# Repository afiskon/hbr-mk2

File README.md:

# HBR/MK2

All HF bands QRP CW/SSB transceiver "HomeBrew Radio, Mark 2".

* Covers 80, 40, 30, 20, 17, 15, 12 and 10 meters
* Classical single IF superheterodyne design
* Effective IF derived AGC
* Voice compression
* Supports RIT and XIT
* 10-30 WPM Elekey-B type keyer + straight key mode
* Keyer supports record and playback, programmable with paddles
* Five favorite frequencies per band (press NEXT/PREV in FAST mode)
* Class AB amplifier provides 5-10W in both CW and SSB
* Has a S-meter and a SWR meter
* Open-source firmware, schematic and 3D-printable enclosure

Links:

* Article (in Russian): https://eax.me/2024/2024-05-12-hbr-mk2-transceiver.html
* Post on Hackaday: https://hackaday.com/2024/05/13/github-hosts-ham-radio/
* Post on DXZone: https://www.dxzone.com/hbr-mk2-hf-qrp-cw-ssb-transceiver/
* Video blog on YouTube: https://www.youtube.com/playlist?list=PL6CWlCy5akj5v1Z4mPysYlqgNtCBYy-wM
* Video blog on Archive.org: https://archive.org/details/hbr-mk2-videos

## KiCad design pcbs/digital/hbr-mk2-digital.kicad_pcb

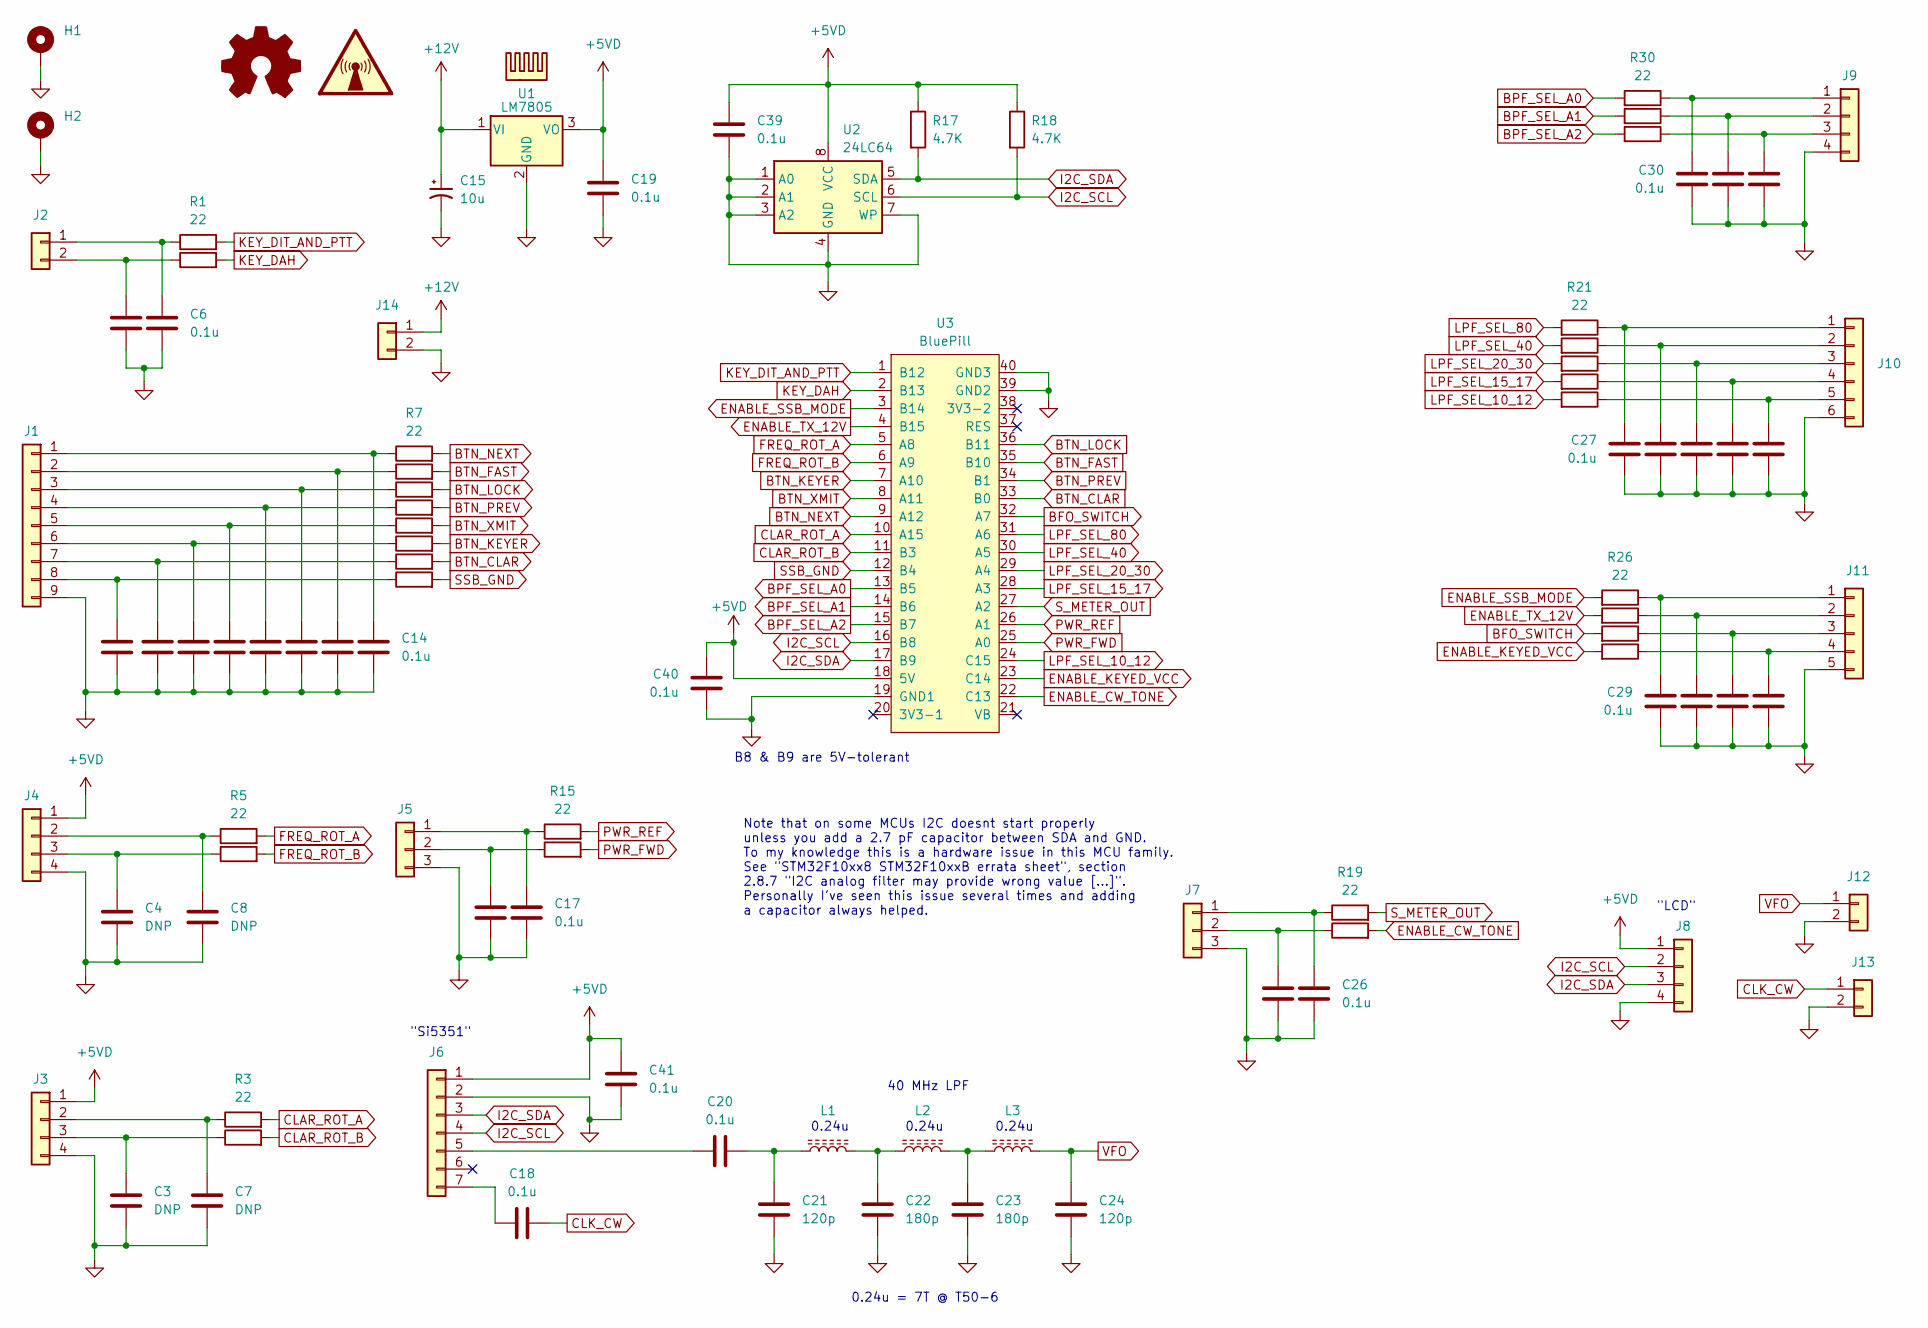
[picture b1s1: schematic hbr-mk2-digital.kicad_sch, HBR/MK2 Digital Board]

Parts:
C1, C2, C5, C6, C9, C10, C11, C12, C13, C14, C16, C17, C18, C19, C20, C25, C26, C27, C28, C29, C30, C31, C32, C33, C34, C35, C36, C37, C38, C39, C40, C41: 0.1u; C_0805_2012Metric_Pad1.18x1.45mm_HandSolder
C3, C4, C7, C8: DNP; C_0805_2012Metric_Pad1.18x1.45mm_HandSolder
C15: 10u; CP_Radial_D5.0mm_P2.50mm
C21, C24: 120p; C_0805_2012Metric_Pad1.18x1.45mm_HandSolder
C22, C23: 180p; C_0805_2012Metric_Pad1.18x1.45mm_HandSolder
H1, H2: MountingHole_Pad; MountingHole_3.5mm_Pad_Via
HS1: Heatsink
J1: Conn_01x09; PinHeader_1x09_P2.54mm_Vertical
J2, J12, J13, J14: Conn_01x02; PinHeader_1x02_P2.54mm_Vertical
J3, J4, J8, J9: Conn_01x04; PinHeader_1x04_P2.54mm_Vertical
J5, J7: Conn_01x03; PinHeader_1x03_P2.54mm_Vertical
J6: Conn_01x07; PinHeader_1x07_P2.54mm_Vertical
J10: Conn_01x06; PinHeader_1x06_P2.54mm_Vertical
J11: Conn_01x05; PinHeader_1x05_P2.54mm_Vertical
L1, L2, L3: T50-6; L_Toroid_Vertical_L13.0mm_W6.5mm_P5.60mm
R1, R2, R3, R4, R5, R6, R7, R8, R9, R10, R11, R12, R13, R14, R15, R16, R19, R20, R21, R22, R23, R24, R25, R26, R27, R28, R29, R30, R31, R32: 22; R_0805_2012Metric_Pad1.20x1.40mm_HandSolder
R17, R18: 4.7K; R_0805_2012Metric_Pad1.20x1.40mm_HandSolder
SYM1: Logo_Open_Hardware_Small; OSHW-Logo2_9.8x8mm_SilkScreen
SYM2: SYM_Radio_Waves_Large; KiCad-Logo2_5mm_SilkScreen
U1: LM7805; TO-220-3_Vertical
U2: 24LC64; SO-8_5.3x6.2mm_P1.27mm
U3: BluePill

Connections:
+5VD: C19.1, C39.1, C40.1, C41.1, J3.1, J4.1, J6.1, J8.1, R17.1, R18.1, U1.3 (VO), U2.8 (VCC), U3.18 (5V)
+12V: C15.1, J14.1, U1.1 (VI)
BFO_SWITCH: R28.2, U3.32 (A7)
BPF_SEL_A0: R30.2, U3.13 (B5)
BPF_SEL_A1: R31.2, U3.14 (B6)
BPF_SEL_A2: R32.2, U3.15 (B7)
BTN_CLAR: R13.2, U3.33 (B0)
BTN_FAST: R8.2, U3.35 (B10)
BTN_KEYER: R12.2, U3.7 (A10)
BTN_LOCK: R9.2, U3.36 (B11)
BTN_NEXT: R7.2, U3.9 (A12)
BTN_PREV: R10.2, U3.34 (B1)
BTN_XMIT: R11.2, U3.8 (A11)
CLAR_ROT_A: R3.2, U3.10 (A15)
CLAR_ROT_B: R4.2, U3.11 (B3)
CLK_CW: C18.2, J13.1
ENABLE_CW_TONE: R20.2, U3.22 (C13)
ENABLE_KEYED_VCC: R29.2, U3.23 (C14)
ENABLE_SSB_MODE: R26.2, U3.3 (B14)
ENABLE_TX_12V: R27.2, U3.4 (B15)
FREQ_ROT_A: R5.2, U3.5 (A8)
FREQ_ROT_B: R6.2, U3.6 (A9)
GND: C1.2, C2.2, C3.2, C4.2, C5.2, C6.2, C7.2, C8.2, C9.2, C10.2, C11.2, C12.2, C13.2, C14.2, C15.2, C16.2, C17.2, C19.2, C21.2, C22.2, C23.2, C24.2, C25.2, C26.2, C27.2, C28.2, C29.2, C30.2, C31.2, C32.2, C33.2, C34.2, C35.2, C36.2, C37.2, C38.2, C39.2, C40.2, C41.2, H1.1, H2.1, J1.9, J3.4, J4.4, J5.3, J6.2, J7.3, J8.4, J9.4, J10.6, J11.5, J12.2, J13.2, J14.2, U1.2 (GND), U2.1 (A0), U2.2 (A1), U2.3 (A2), U2.4 (GND), U2.7 (WP), U3.19 (GND1), U3.39 (GND2), U3.40 (GND3)
I2C_SCL: J6.4, J8.2, R18.2, U2.6 (SCL), U3.16 (B8)
I2C_SDA: J6.3, J8.3, R17.2, U2.5 (SDA), U3.17 (B9)
KEY_DAH: R2.2, U3.2 (B13)
KEY_DIT_AND_PTT: R1.2, U3.1 (B12)
LPF_SEL_10_12: R25.2, U3.24 (C15)
LPF_SEL_15_17: R24.2, U3.28 (A3)
LPF_SEL_20_30: R23.2, U3.29 (A4)
LPF_SEL_40: R22.2, U3.30 (A5)
LPF_SEL_80: R21.2, U3.31 (A6)
unnamed: C20.2, C21.1, L1.1
unnamed: C22.1, L1.2, L2.1
unnamed: C23.1, L2.2, L3.1
unnamed: C14.1, J1.1, R7.1
unnamed: C13.1, J1.2, R8.1
unnamed: C12.1, J1.3, R9.1
unnamed: C11.1, J1.4, R10.1
unnamed: C10.1, J1.5, R11.1
unnamed: C9.1, J1.6, R12.1
unnamed: C5.1, J1.7, R13.1
unnamed: C1.1, J1.8, R14.1
unnamed: C6.1, J2.1, R1.1
unnamed: C2.1, J2.2, R2.1
unnamed: C7.1, J3.2, R3.1
unnamed: C3.1, J3.3, R4.1
unnamed: C8.1, J4.2, R5.1
unnamed: C4.1, J4.3, R6.1
unnamed: C17.1, J5.1, R15.1
unnamed: C16.1, J5.2, R16.1
unnamed: C20.1, J6.5
unnamed: C18.1, J6.7
unnamed: C26.1, J7.1, R19.1
unnamed: C25.1, J7.2, R20.1
unnamed: C30.1, J9.1, R30.1
unnamed: C33.1, J9.2, R31.1
unnamed: C36.1, J9.3, R32.1
unnamed: C27.1, J10.1, R21.1
unnamed: C28.1, J10.2, R22.1
unnamed: C31.1, J10.3, R23.1
unnamed: C34.1, J10.4, R24.1
unnamed: C37.1, J10.5, R25.1
unnamed: C29.1, J11.1, R26.1
unnamed: C32.1, J11.2, R27.1
unnamed: C35.1, J11.3, R28.1
unnamed: C38.1, J11.4, R29.1
PWR_FWD: R16.2, U3.25 (A0)
PWR_REF: R15.2, U3.26 (A1)
SSB_GND: R14.2, U3.12 (B4)
S_METER_OUT: R19.2, U3.27 (A2)
VFO: C24.1, J12.1, L3.2

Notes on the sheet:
0.24u = 7T @ T50-6
0.24u
40 MHz LPF
"Si5351"
"LCD"
B8 & B9 are 5V-tolerant
Note that on some MCUs I2C doesnt start properly unless you add a 2.7 pF capacitor between SDA and GND. To my knowledge this is a hardware issue in this MCU family. See "STM32F10xx8 STM32F10xxB errata sheet", section 2.8.7 "I2C analog filter may provide wrong value [...]". Personally I've seen this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

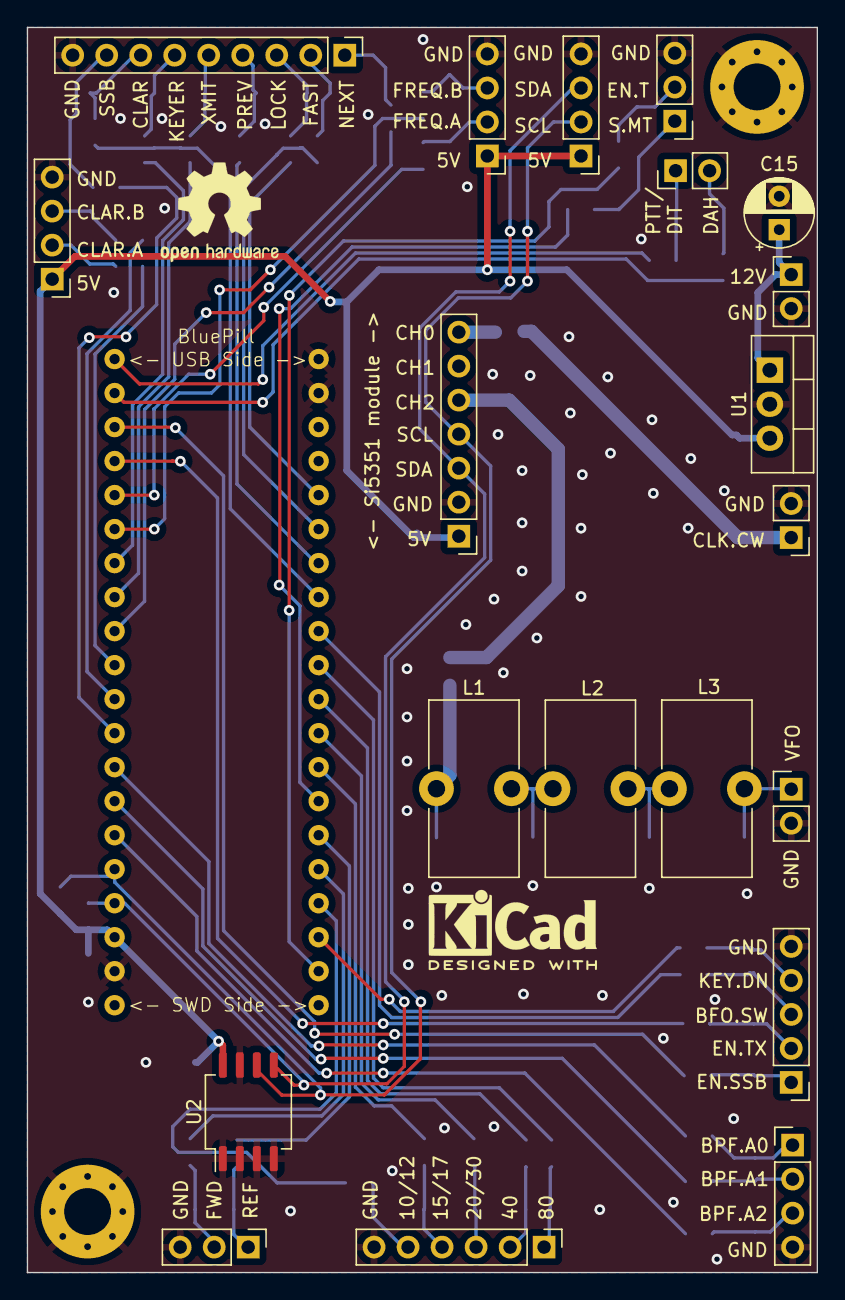
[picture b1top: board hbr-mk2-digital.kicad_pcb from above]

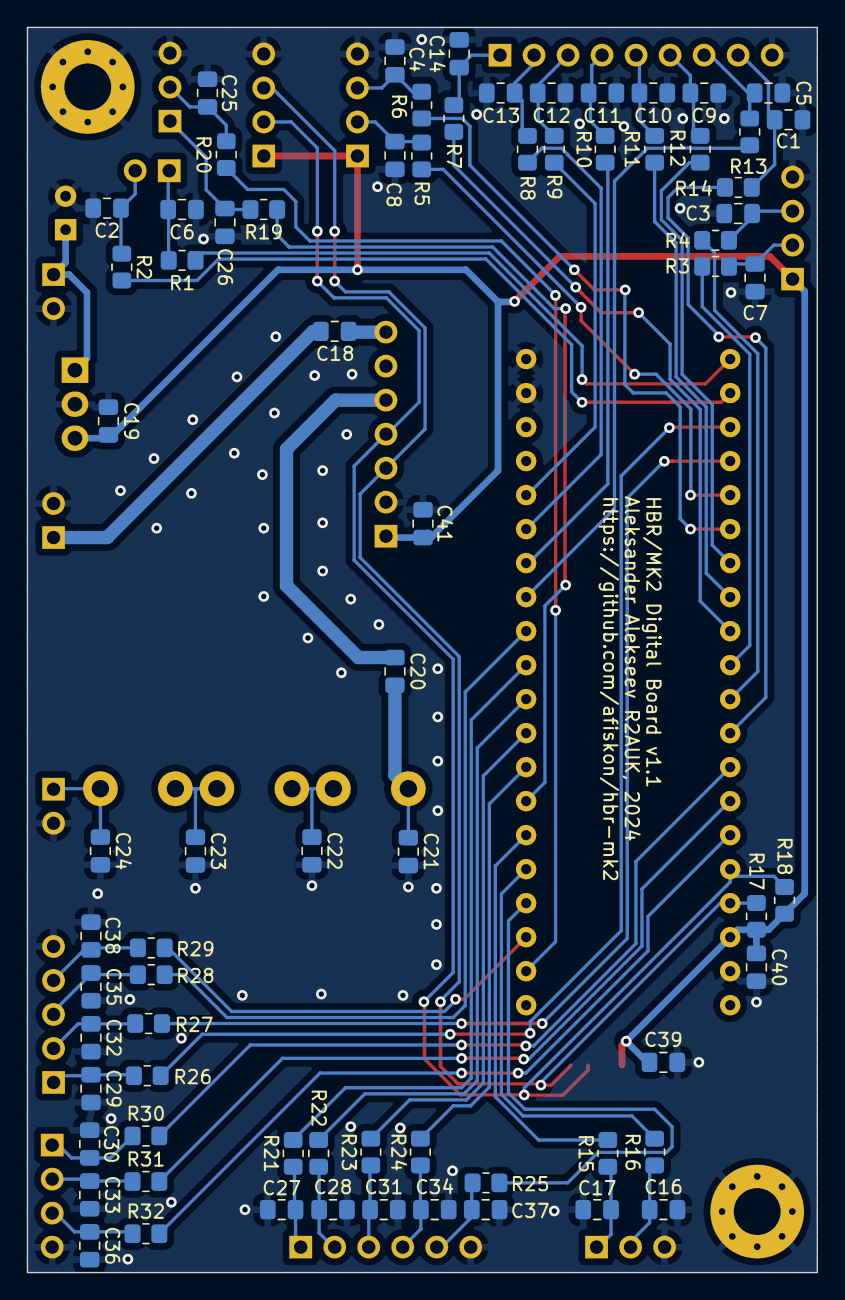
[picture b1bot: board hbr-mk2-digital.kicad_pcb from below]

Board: 2 copper layers, 59.0 x 93.0 mm, 97 parts (72 on the bottom side), 72 nets.

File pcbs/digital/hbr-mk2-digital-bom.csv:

Reference(s),Qty,Value,Footprint
"C1, C2, C5, C6, C9, C10, C11, C12, C13, C14, C16, C17, C18, C19, C20, C25, C26, C27, C28, C29, C30, C31, C32, C33, C34, C35, C36, C37, C38, C39, C40, C41",32,0.1u,Capacitor_SMD:C_0805_2012Metric_Pad1.18x1.45mm_HandSolder
C15,1,10u,Capacitor_THT:CP_Radial_D5.0mm_P2.50mm
"C21, C24",2,120p,Capacitor_SMD:C_0805_2012Metric_Pad1.18x1.45mm_HandSolder
"C22, C23",2,180p,Capacitor_SMD:C_0805_2012Metric_Pad1.18x1.45mm_HandSolder
J6,1,Si5351 Module,Connector_PinHeader_2.54mm:PinHeader_1x07_P2.54mm_Vertical
"L1, L2, L3",3,T50-6,Inductor_THT:L_Toroid_Vertical_L13.0mm_W6.5mm_P5.60mm
"R1, R2, R3, R4, R5, R6, R7, R8, R9, R10, R11, R12, R13, R14, R15, R16, R19, R20, R21, R22, R23, R24, R25, R26, R27, R28, R29, R30, R31, R32",30,22,Resistor_SMD:R_0805_2012Metric_Pad1.20x1.40mm_HandSolder
"R17, R18",2,4.7K,Resistor_SMD:R_0805_2012Metric_Pad1.20x1.40mm_HandSolder
U1,1,LM7805,Package_TO_SOT_THT:TO-220-3_Vertical
U2,1,24LC64,Package_SO:SO-8_5.3x6.2mm_P1.27mm
U3,1,BluePill,My_Library:BluePill

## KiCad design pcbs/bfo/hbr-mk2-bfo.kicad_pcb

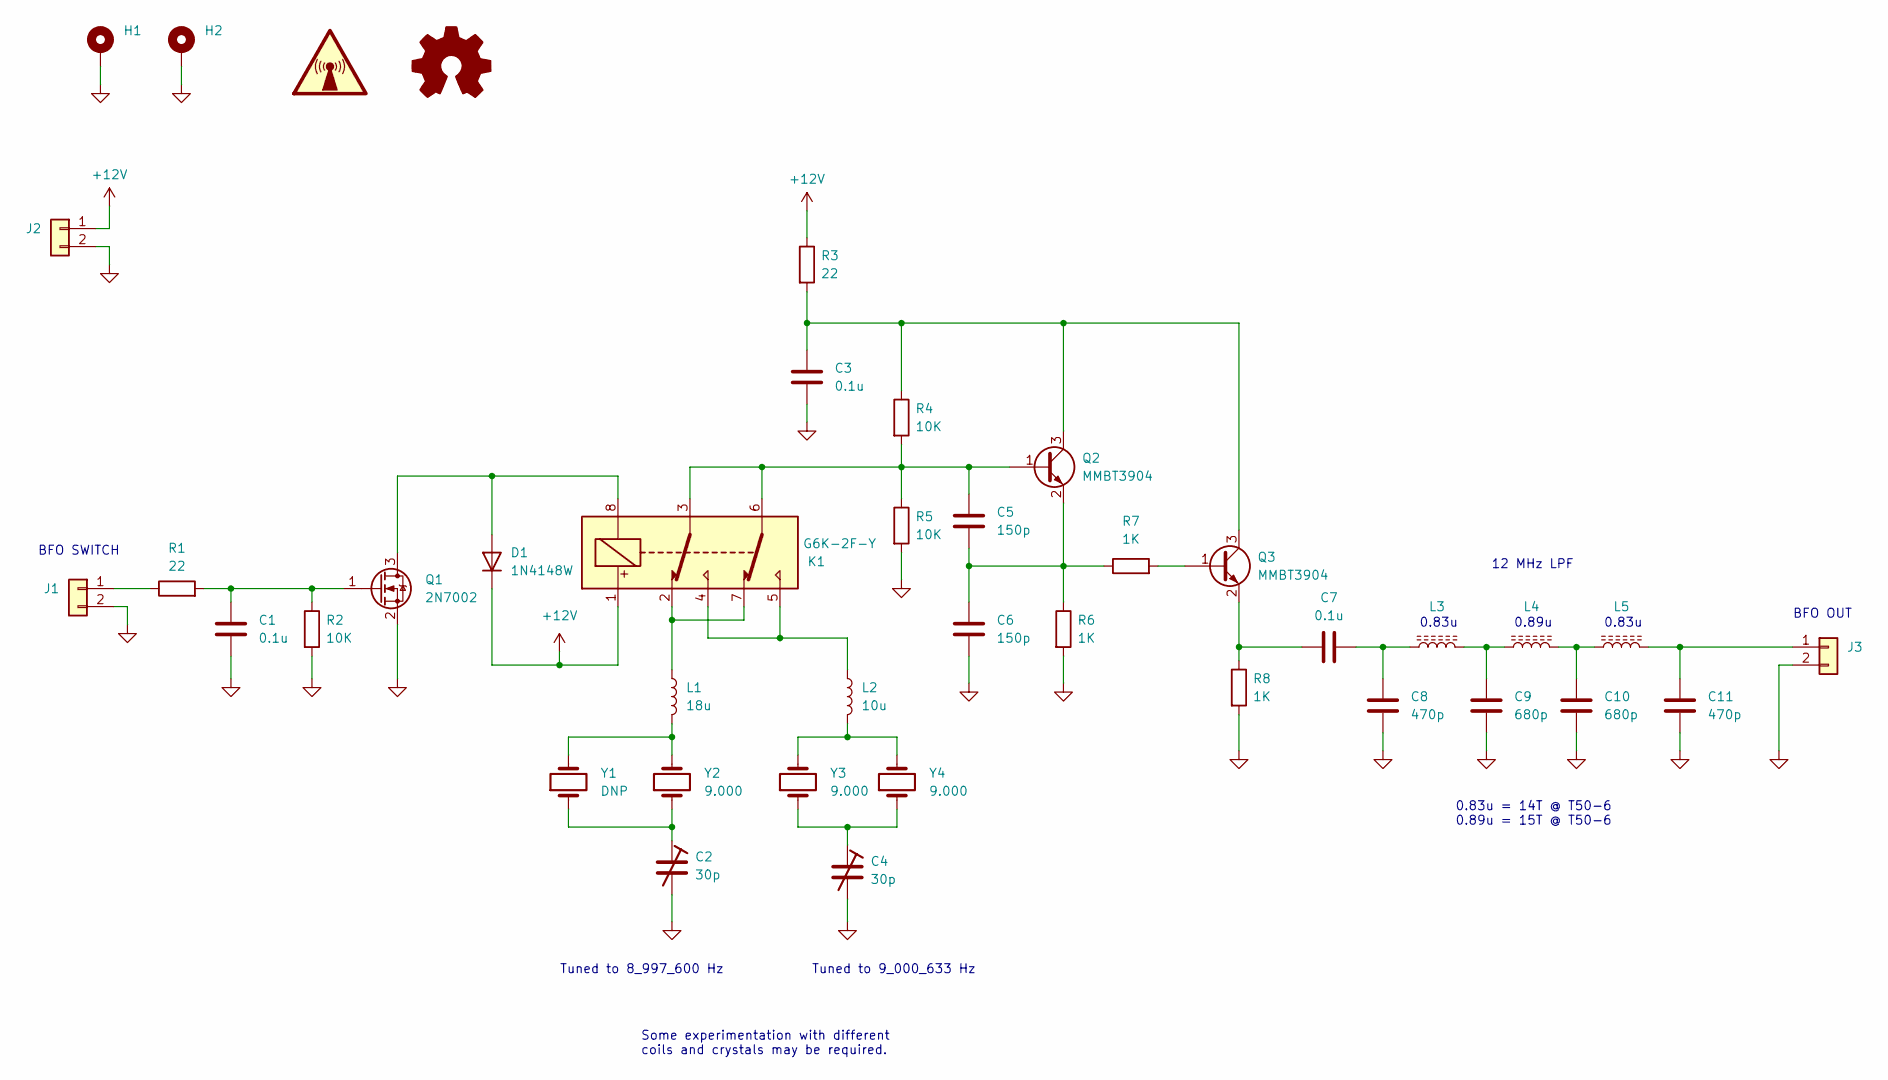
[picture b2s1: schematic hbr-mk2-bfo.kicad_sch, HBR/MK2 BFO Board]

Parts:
C1, C3, C7: 0.1u; C_0805_2012Metric_Pad1.18x1.45mm_HandSolder
C2, C4: 30p; C_Trim_THD_L7.0mm_W6.5mm_P5.00mm
C5, C6: 150p; C_0805_2012Metric_Pad1.18x1.45mm_HandSolder
C8, C11: 470p; C_0805_2012Metric_Pad1.18x1.45mm_HandSolder
C9, C10: 680p; C_0805_2012Metric_Pad1.18x1.45mm_HandSolder
D1: 1N4148W; D_SOD-123
H1, H2: MountingHole_Pad; MountingHole_3.5mm_Pad_Via
J1, J2, J3: Conn_01x02; PinHeader_1x02_P2.54mm_Vertical
K1: G6K-2F-Y; Relay_DPDT_Omron_G6K-2F-Y
L1: 18u; L_Axial_L7.0mm_D3.3mm_P12.70mm_Horizontal_Fastron_MICC
L2: 10u; L_Axial_L7.0mm_D3.3mm_P12.70mm_Horizontal_Fastron_MICC
L3, L4, L5: T50-6; L_Toroid_Vertical_L13.0mm_W6.5mm_P5.60mm
Q1: 2N7002; SOT-23
Q2, Q3: MMBT3904; SOT-23
R1, R3: 22; R_0805_2012Metric_Pad1.20x1.40mm_HandSolder
R2, R4, R5: 10K; R_0805_2012Metric_Pad1.20x1.40mm_HandSolder
R6, R7, R8: 1K; R_0805_2012Metric_Pad1.20x1.40mm_HandSolder
SYM1: SYM_Radio_Waves_Large; KiCad-Logo2_5mm_SilkScreen
SYM2: Logo_Open_Hardware_Small; OSHW-Logo2_9.8x8mm_SilkScreen
Y1: DNP; Crystal_HC49-U_Vertical
Y2, Y3, Y4: 9.000; Crystal_HC49-U_Vertical

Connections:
+12V: D1.1 (K), J2.1, K1.1, R3.1
GND: C1.2, C2.2, C3.2, C4.2, C6.2, C8.2, C9.2, C10.2, C11.2, H1.1, H2.1, J1.2, J2.2, J3.2, Q1.2 (S), R2.2, R5.2, R6.2, R8.2
unnamed: C2.1, Y1.1, Y2.1
unnamed: C4.1, Y3.1, Y4.1
unnamed: C7.2, C8.1, L3.1
unnamed: C9.1, L3.2, L4.1
unnamed: C10.1, L4.2, L5.1
unnamed: D1.2 (A), K1.8, Q1.3 (D)
unnamed: J1.1, R1.1
unnamed: C11.1, J3.1, L5.2
unnamed: K1.2, K1.7, L1.1
unnamed: K1.4, K1.5, L2.1
unnamed: L1.2, Y1.2, Y2.2
unnamed: L2.2, Y3.2, Y4.2
unnamed: C1.1, Q1.1 (G), R1.2, R2.1
unnamed: C5.1, K1.3, K1.6, Q2.1 (B), R4.2, R5.1
unnamed: C3.1, Q2.3 (C), Q3.3 (C), R3.2, R4.1
unnamed: C5.2, C6.1, Q2.2 (E), R6.1, R7.1
unnamed: Q3.1 (B), R7.2
unnamed: C7.1, Q3.2 (E), R8.1

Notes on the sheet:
BFO SWITCH
Some experimentation with different coils and crystals may be required.
0.83u
Tuned to 9_000_633 Hz
0.89u
Tuned to 8_997_600 Hz
12 MHz LPF
0.83u = 14T @ T50-6 0.89u = 15T @ T50-6
BFO OUT

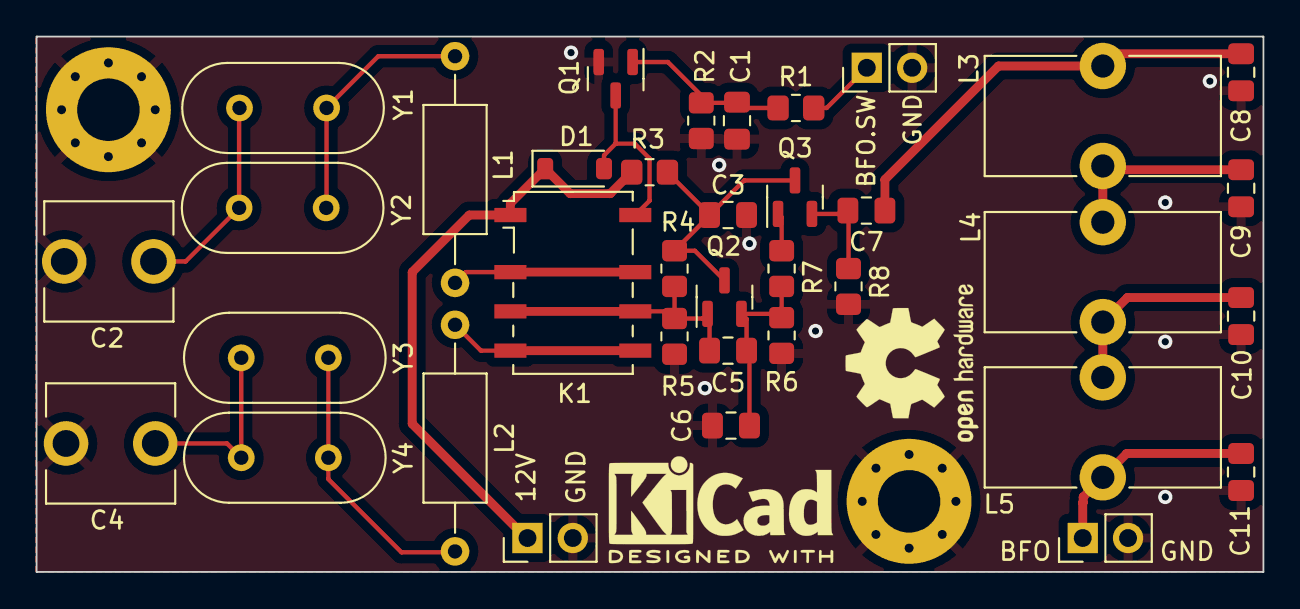
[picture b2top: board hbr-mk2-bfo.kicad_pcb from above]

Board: 2 copper layers, 68.8 x 30.0 mm, 40 parts (0 on the bottom side), 20 nets.

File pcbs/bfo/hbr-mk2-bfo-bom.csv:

Reference(s),Qty,Value,Footprint
"C1, C3, C7",3,0.1u,Capacitor_SMD:C_0805_2012Metric_Pad1.18x1.45mm_HandSolder
"C2, C4",2,30p,My_Library:C_Trim_THD_L7.0mm_W6.5mm_P5.00mm
"C5, C6",2,150p,Capacitor_SMD:C_0805_2012Metric_Pad1.18x1.45mm_HandSolder
"C8, C11",2,470p,Capacitor_SMD:C_0805_2012Metric_Pad1.18x1.45mm_HandSolder
"C9, C10",2,680p,Capacitor_SMD:C_0805_2012Metric_Pad1.18x1.45mm_HandSolder
D1,1,1N4148W,Diode_SMD:D_SOD-123
K1,1,G6K-2F-Y,Relay_SMD:Relay_DPDT_Omron_G6K-2F-Y
L1,1,18u,Inductor_THT:L_Axial_L7.0mm_D3.3mm_P12.70mm_Horizontal_Fastron_MICC
L2,1,10u,Inductor_THT:L_Axial_L7.0mm_D3.3mm_P12.70mm_Horizontal_Fastron_MICC
"L3, L4, L5",3,T50-6,Inductor_THT:L_Toroid_Vertical_L13.0mm_W6.5mm_P5.60mm
Q1,1,2N7002,Package_TO_SOT_SMD:SOT-23
"Q2, Q3",2,MMBT3904,Package_TO_SOT_SMD:SOT-23
"R1, R3",2,22,Resistor_SMD:R_0805_2012Metric_Pad1.20x1.40mm_HandSolder
"R2, R4, R5",3,10K,Resistor_SMD:R_0805_2012Metric_Pad1.20x1.40mm_HandSolder
"R6, R7, R8",3,1K,Resistor_SMD:R_0805_2012Metric_Pad1.20x1.40mm_HandSolder
"Y2, Y3, Y4",3,9,Crystal:Crystal_HC49-U_Vertical

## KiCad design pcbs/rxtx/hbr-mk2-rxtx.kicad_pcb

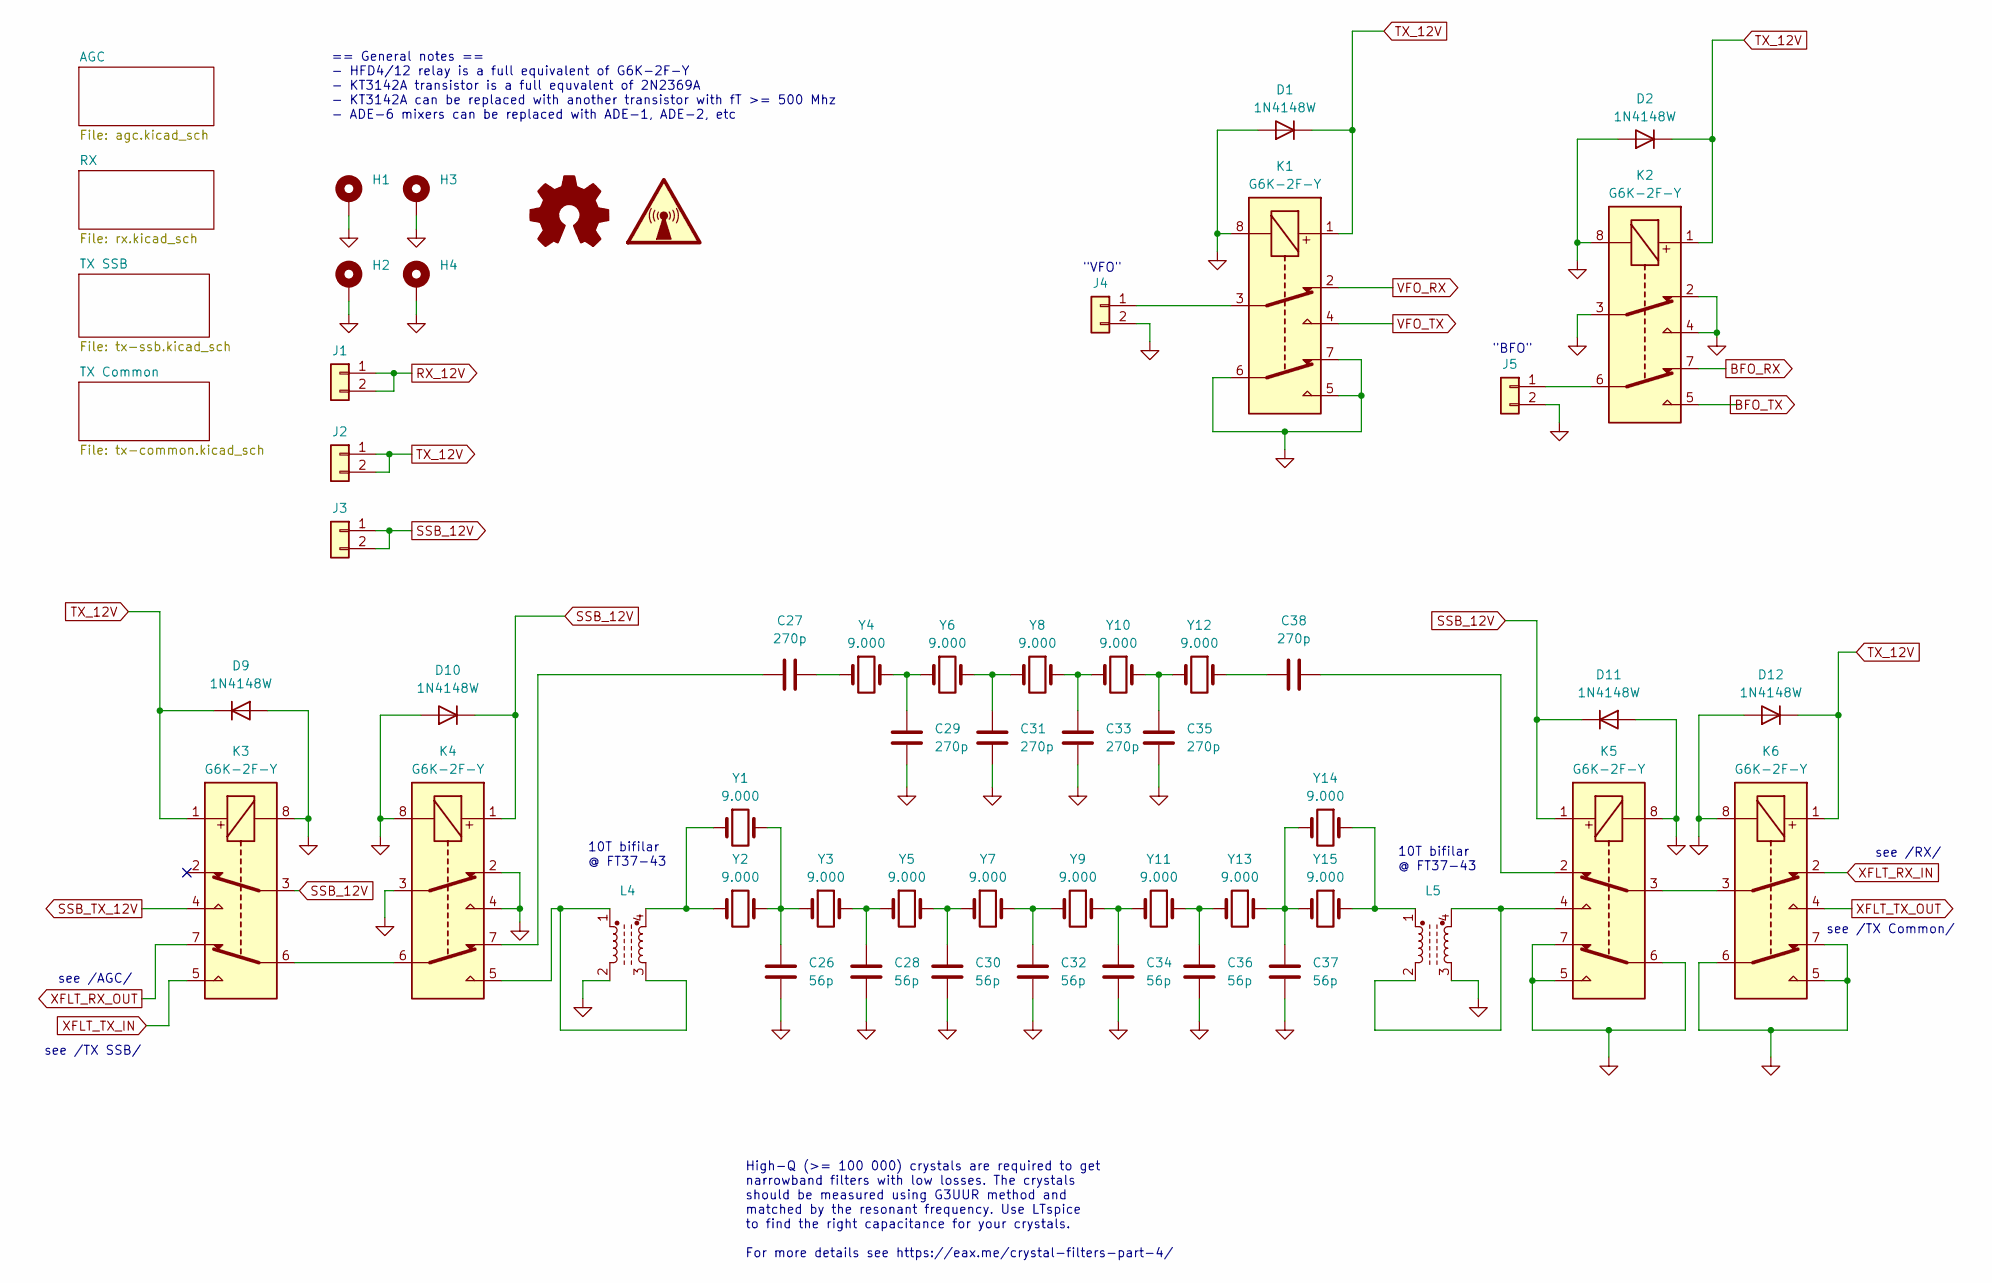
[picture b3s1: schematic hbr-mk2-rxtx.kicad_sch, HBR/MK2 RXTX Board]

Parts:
C26, C28, C30, C32, C34, C36, C37: 56p; C_0805_2012Metric_Pad1.18x1.45mm_HandSolder
C27, C29, C31, C33, C35, C38: 270p; C_0805_2012Metric_Pad1.18x1.45mm_HandSolder
D1, D2, D9, D10, D11, D12: 1N4148W; D_SOD-123
H1, H2, H3, H4: MountingHole_Pad; MountingHole_3.5mm_Pad_Via
J1, J2, J3, J4, J5: Conn_01x02; PinHeader_1x02_P2.54mm_Vertical
K1, K2, K3, K4, K5, K6: G6K-2F-Y; Relay_DPDT_Omron_G6K-2F-Y
L4, L5: FT37-43; DIP-4_W7.62mm
SYM1: Logo_Open_Hardware_Small; OSHW-Logo2_9.8x8mm_SilkScreen
SYM2: SYM_Radio_Waves_Large; KiCad-Logo2_5mm_SilkScreen
Y1, Y2, Y3, Y4, Y5, Y6, Y7, Y8, Y9, Y10, Y11, Y12, Y13, Y14, Y15: 9.000; Crystal_HC49-U_Vertical

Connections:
BFO_RX: K2.7; also elsewhere on the board
BFO_TX: K2.5; also elsewhere on the board
GND: C26.2, C28.2, C29.2, C30.2, C31.2, C32.2, C33.2, C34.2, C35.2, C36.2, C37.2, D1.2 (A), D2.2 (A), D9.2 (A), D10.2 (A), D11.2 (A), D12.2 (A), H1.1, H2.1, H3.1, H4.1, J4.2, J5.2, K1.5, K1.6, K1.7, K1.8, K2.2, K2.3, K2.4, K2.8, K3.8, K4.2, K4.3, K4.4, K4.8, K5.5, K5.6, K5.7, K5.8, K6.5, K6.6, K6.7, K6.8, L4.2, L5.3; also elsewhere on the board
unnamed: C26.1, Y1.2, Y2.2, Y3.1
unnamed: C27.1, K4.7
unnamed: C27.2, Y4.1
unnamed: C28.1, Y3.2, Y5.1
unnamed: C29.1, Y4.2, Y6.1
unnamed: C30.1, Y5.2, Y7.1
unnamed: C31.1, Y6.2, Y8.2
unnamed: C32.1, Y7.2, Y9.2
unnamed: C33.1, Y8.1, Y10.2
unnamed: C34.1, Y9.1, Y11.2
unnamed: C35.1, Y10.1, Y12.2
unnamed: C36.1, Y11.1, Y13.2
unnamed: C37.1, Y13.1, Y14.2, Y15.2
unnamed: C38.1, Y12.1
unnamed: C38.2, K5.2
unnamed: J4.1, K1.3
unnamed: J5.1, K2.6
unnamed: K3.6, K4.6
unnamed: K4.5, L4.1, L4.3
unnamed: K5.3, K6.3
unnamed: K5.4, L5.2, L5.4
unnamed: L4.4, Y1.1, Y2.1
unnamed: L5.1, Y14.1, Y15.1
RX_12V: J1.1, J1.2; also elsewhere on the board
SSB_12V: D10.1 (K), D11.1 (K), J3.1, J3.2, K3.3, K4.1, K5.1
SSB_TX_12V: K3.4; also elsewhere on the board
TX_12V: D1.1 (K), D2.1 (K), D9.1 (K), D12.1 (K), J2.1, J2.2, K1.1, K2.1, K3.1, K6.1; also elsewhere on the board
VFO_RX: K1.2; also elsewhere on the board
VFO_TX: K1.4; also elsewhere on the board
XFLT_RX_IN: K6.2; also elsewhere on the board
XFLT_RX_OUT: K3.7; also elsewhere on the board
XFLT_TX_IN: K3.5; also elsewhere on the board
XFLT_TX_OUT: K6.4; also elsewhere on the board

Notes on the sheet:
10T bifilar @ FT37-43
High-Q (>= 100 000) crystals are required to get narrowband filters with low losses. The crystals should be measured using G3UUR method and matched by the resonant frequency. Use LTspice to find the right capacitance for your crystals. For more details see https://eax.me/crystal-filters-part-4/
see /TX SSB/
== General notes == - HFD4/12 relay is a full equivalent of G6K-2F-Y - KT3142A transistor is a full equvalent of 2N2369A - KT3142A can be replaced with another transistor with fT >= 500 Mhz - ADE-6 mixers can be replaced with ADE-1, ADE-2, etc
see /RX/
see /AGC/
see /TX Common/
"VFO"
"BFO"

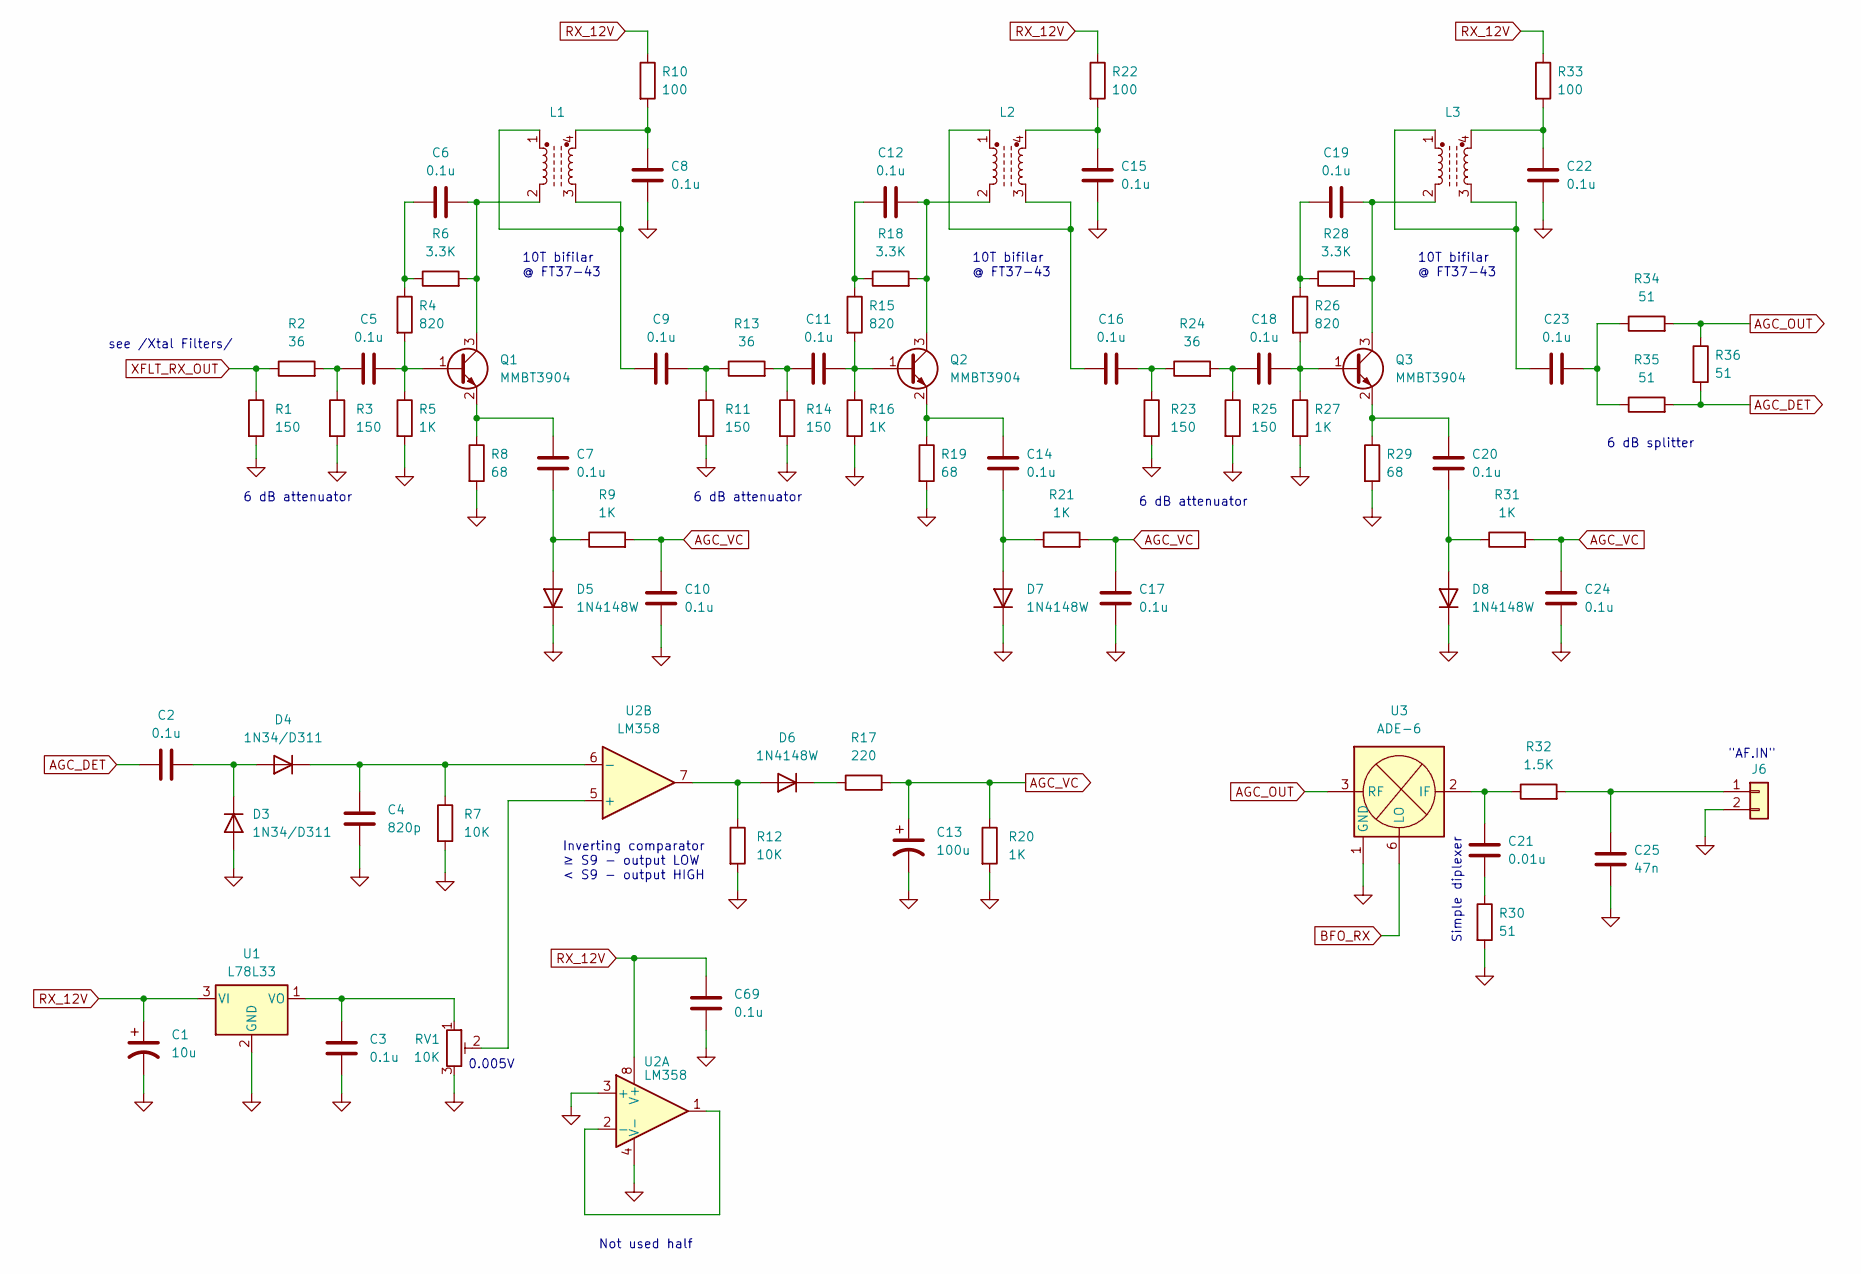
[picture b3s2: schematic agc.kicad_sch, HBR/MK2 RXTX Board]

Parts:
C1: 10u; CP_Elec_4x5.4
C2, C3, C5, C6, C7, C8, C9, C10, C11, C12, C14, C15, C16, C17, C18, C19, C20, C22, C23, C24, C69: 0.1u; C_0805_2012Metric_Pad1.18x1.45mm_HandSolder
C4: 820p; C_0805_2012Metric_Pad1.18x1.45mm_HandSolder
C13: 100u; CP_Elec_6.3x7.7
C21: 0.01u; C_0805_2012Metric_Pad1.18x1.45mm_HandSolder
C25: 47n; C_0805_2012Metric_Pad1.18x1.45mm_HandSolder
D3, D4: 1N34/D311; D_DO-34_SOD68_P2.54mm_Vertical_AnodeUp
D5, D6, D7, D8: 1N4148W; D_SOD-123
J6: Conn_01x02; PinHeader_1x02_P2.54mm_Vertical
L1, L2, L3: FT37-43; DIP-4_W7.62mm
Q1, Q2, Q3: MMBT3904; SOT-23
R1, R3, R11, R14, R23, R25: 150; R_0805_2012Metric_Pad1.20x1.40mm_HandSolder
R2, R13, R24: 36; R_0805_2012Metric_Pad1.20x1.40mm_HandSolder
R4, R15, R26: 820; R_0805_2012Metric_Pad1.20x1.40mm_HandSolder
R5, R9, R16, R20, R21, R27, R31: 1K; R_0805_2012Metric_Pad1.20x1.40mm_HandSolder
R6, R18, R28: 3.3K; R_0805_2012Metric_Pad1.20x1.40mm_HandSolder
R7, R12: 10K; R_0805_2012Metric_Pad1.20x1.40mm_HandSolder
R8, R19, R29: 68; R_0805_2012Metric_Pad1.20x1.40mm_HandSolder
R10, R22, R33: 100; R_0805_2012Metric_Pad1.20x1.40mm_HandSolder
R17: 220; R_0805_2012Metric_Pad1.20x1.40mm_HandSolder
R30, R34, R35, R36: 51; R_0805_2012Metric_Pad1.20x1.40mm_HandSolder
R32: 1.5K; R_0805_2012Metric_Pad1.20x1.40mm_HandSolder
RV1: 10K; Potentiometer_Bourns_3296W_Vertical
U1: L78L33; TO-92_HandSolder
U2: LM358; SOIC-8_5.23x5.23mm_P1.27mm
U3: ADE-6; Mini-Circuits_CD542_LandPatternPL-052

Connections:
AGC_DET: C2.1, R35.2, R36.2
AGC_OUT: R34.2, R36.1, U3.3 (RF)
AGC_VC: C10.2, C13.1, C17.2, C24.2, R9.2, R17.2, R20.1, R21.2, R31.2
BFO_RX: U3.6 (LO); also elsewhere on the board
GND: C1.2, C3.1, C4.1, C8.1, C10.1, C13.2, C15.1, C17.1, C22.1, C24.1, C25.1, C69.1, D3.2 (A), D5.1 (K), D7.1 (K), D8.1 (K), J6.2, R1.2, R3.2, R5.2, R7.2, R8.2, R11.2, R12.2, R14.2, R16.2, R19.2, R20.2, R23.2, R25.2, R27.2, R29.2, R30.2, RV1.3, U1.2 (GND), U2.3 (+), U2.4 (V-), U3.1 (GND), U3.4 (GND), U3.5 (GND); also elsewhere on the board
unnamed: C5.1, R2.2, R3.1
unnamed: C6.1, R4.1, R6.1
unnamed: C8.2, L1.4, R10.2
unnamed: C9.1, L1.1, L1.3
unnamed: C9.2, R11.1, R13.1
unnamed: C11.1, R13.2, R14.1
unnamed: C12.1, R15.1, R18.1
unnamed: C15.2, L2.4, R22.2
unnamed: C16.1, L2.1, L2.3
unnamed: C16.2, R23.1, R24.1
unnamed: C18.1, R24.2, R25.1
unnamed: C19.1, R26.1, R28.1
unnamed: C21.1, R30.1
unnamed: C22.2, L3.4, R33.2
unnamed: C23.1, L3.1, L3.3
unnamed: C23.2, R34.1, R35.1
unnamed: C2.2, D3.1 (K), D4.2 (A)
unnamed: C4.2, D4.1 (K), R7.1, U2.6 (-)
unnamed: C7.1, D5.2 (A), R9.1
unnamed: D6.2 (A), R12.1, U2.7
unnamed: D6.1 (K), R17.1
unnamed: C14.1, D7.2 (A), R21.1
unnamed: C20.1, D8.2 (A), R31.1
unnamed: C25.2, J6.1, R32.2
unnamed: C5.2, Q1.1 (B), R4.2, R5.1
unnamed: C6.2, L1.2, Q1.3 (C), R6.2
unnamed: C7.2, Q1.2 (E), R8.1
unnamed: C11.2, Q2.1 (B), R15.2, R16.1
unnamed: C12.2, L2.2, Q2.3 (C), R18.2
unnamed: C14.2, Q2.2 (E), R19.1
unnamed: C18.2, Q3.1 (B), R26.2, R27.1
unnamed: C19.2, L3.2, Q3.3 (C), R28.2
unnamed: C20.2, Q3.2 (E), R29.1
unnamed: C3.2, RV1.1, U1.1 (VO)
unnamed: U2.1, U2.2 (-)
unnamed: RV1.2, U2.5 (+)
unnamed: C21.2, R32.1, U3.2 (IF)
RX_12V: C1.1, C69.2, R10.1, R22.1, R33.1, U1.3 (VI), U2.8 (V+); also elsewhere on the board
XFLT_RX_OUT: R1.1, R2.1; also elsewhere on the board

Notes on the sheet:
Inverting comparator ≥ S9 - output LOW < S9 - output HIGH
6 dB attenuator
0.005V
see /Xtal Filters/
6 dB splitter
Simple diplexer
10T bifilar @ FT37-43
Not used half
"AF.IN"
